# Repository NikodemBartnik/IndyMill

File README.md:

IndyMill is an open source DIY CNC machine that is mostly made out of metal. It was designed with simplicity and minimalism in mind! 
This project is not aiming to be the most heavy duty CNC machine out there, it is meant to be easy and inexpensive to build so that anyone can get a hand on precise CNC machining in many materials including metal.
Designed by [Nikodem Bartnik](https://www.youtube.com/nikodembartnik). 

Here are just some of the features of this machine:

  - Aluminium profiles (2080 and 2040)
  - Compatible with Nema17 and Nema23 on X and Y axis (without redesigning a plate Z axis is only compatible with Nema23)
  - Made with ball screws, linear rails and 6mm steel plates to ensure rigidity
  - Can be easily scaled up, you just need to use longer profiles, ballscrews and linear rails

***

### You can find more info at [Indystry.cc](https://indystry.cc/)

***

## Open Source
This machine is open source, so above you can find all of the files that you need to build it. You can also check out videos below to see the build process. As for now, the machine was tested with various kinds of wood, MDF, acrylic and aluminium. It is able to machine all of those materials even with a small 500W spindle.
You can also find more information on my website: [Indystry.cc](https://indystry.cc/indymill/)

## Parts

You can find parts list in PDF or XLSX above but you can also find it here:
  - At [indystry.cc/indymill](https://indystry.cc/indymill) you can find a full table with all needed parts
  - [Google Drive Parts List](https://docs.google.com/spreadsheets/d/19kC1wDViL0N2BjQgnNMfYSCzLNLKAHwQCY5Ngf8wU5I) here you can find an online parts list 
  - You can buy some of the parts on my [store](https://indystry.cc/store/)

## Videos

## Build Instruction
This project is open source so you can find all the files that you need to build it above for free. You can easily build it just by taking a look at some images on my website and my videos.
But if you would like to get a PDF instruction that simplifies the build process, you can easily print it put or it on a smartphone or computer. You can get one through link below and at the same time support my projects! You don't need it but it may help a little :)

### https://gum.co/indymill

### Todos

 - Design a better, bigger cable chain

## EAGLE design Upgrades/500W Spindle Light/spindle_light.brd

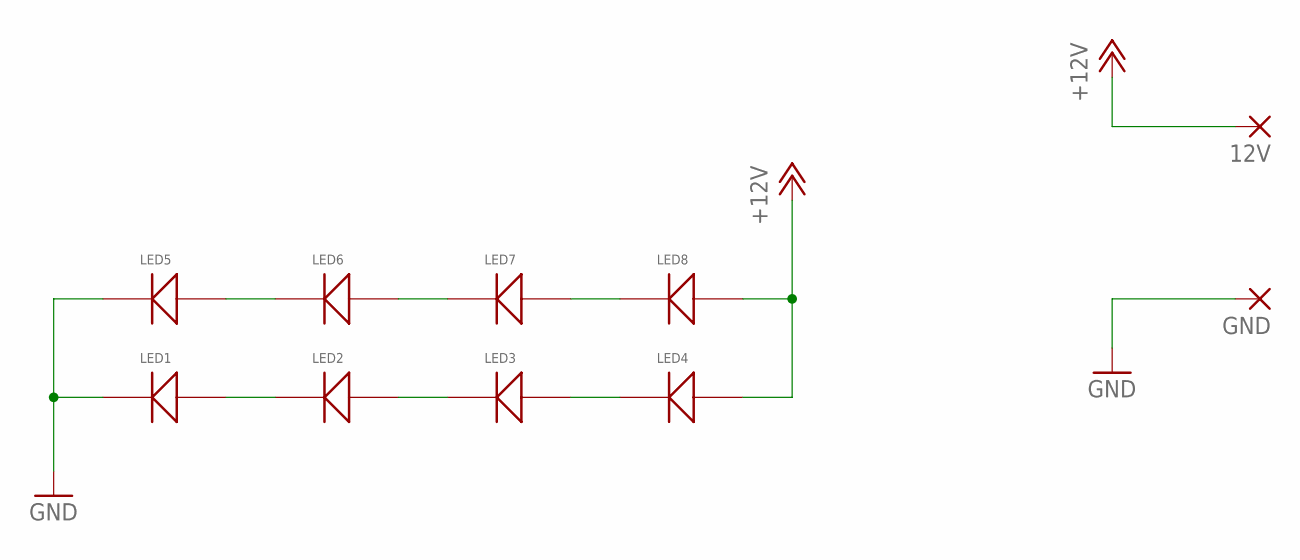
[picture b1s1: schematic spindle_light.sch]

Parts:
12V: SMD5; SMD2,54-5,08
GND: SMD5; SMD2,54-5,08
LED1, LED2, LED3, LED4, LED5, LED6, LED7, LED8: RF-45HA50DS-EE-Y; 5050LED

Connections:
+12V: 12V.1, LED4.P$4, LED4.P$5, LED4.P$6, LED8.P$4, LED8.P$5, LED8.P$6
GND: GND.1, LED1.P$1, LED1.P$2, LED1.P$3, LED5.P$1, LED5.P$2, LED5.P$3
unnamed: LED5.P$4, LED5.P$5, LED5.P$6, LED6.P$1, LED6.P$2, LED6.P$3
unnamed: LED1.P$4, LED1.P$5, LED1.P$6, LED2.P$1, LED2.P$2, LED2.P$3
unnamed: LED2.P$4, LED2.P$5, LED2.P$6, LED3.P$1, LED3.P$2, LED3.P$3
unnamed: LED6.P$4, LED6.P$5, LED6.P$6, LED7.P$1, LED7.P$2, LED7.P$3
unnamed: LED7.P$4, LED7.P$5, LED7.P$6, LED8.P$1, LED8.P$2, LED8.P$3
unnamed: LED3.P$4, LED3.P$5, LED3.P$6, LED4.P$1, LED4.P$2, LED4.P$3

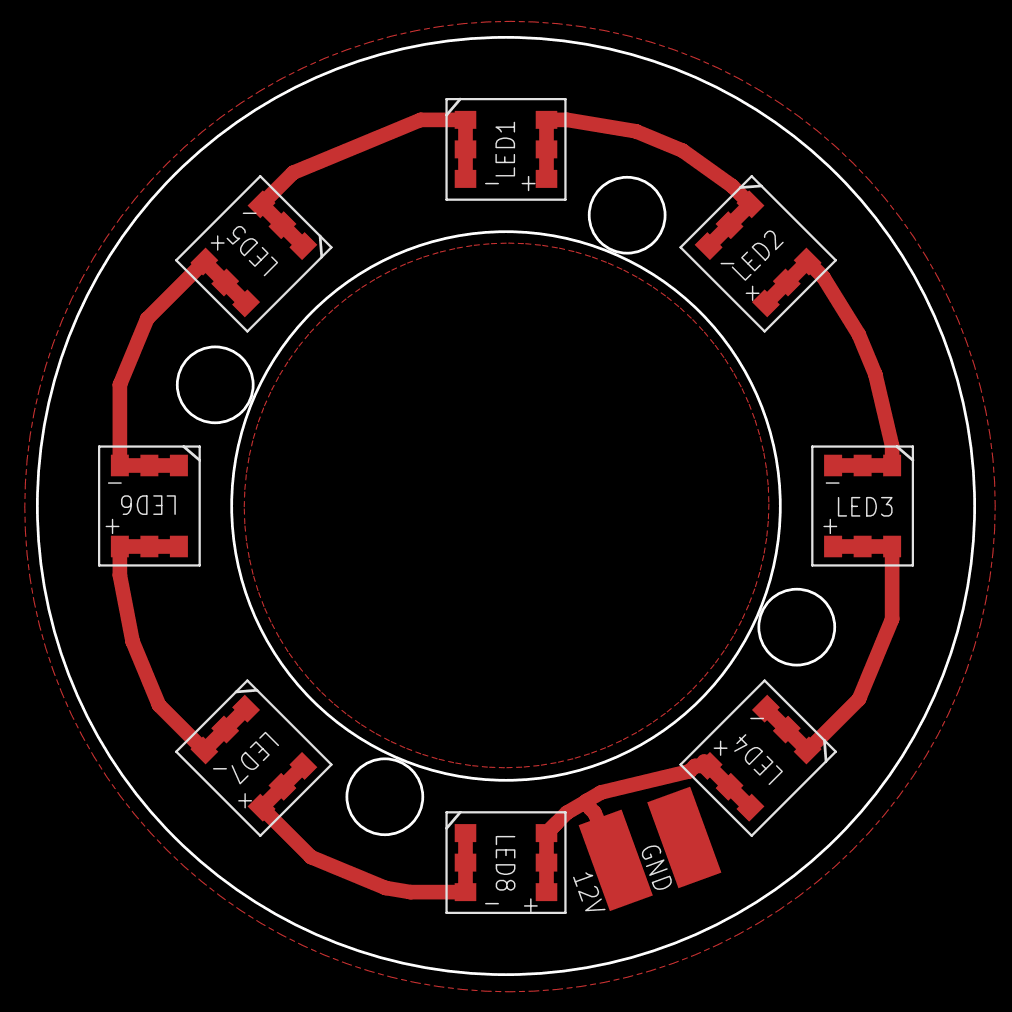
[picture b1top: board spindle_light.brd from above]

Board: 2 copper layers, 52.1 x 52.1 mm, 10 parts (0 on the bottom side), 8 nets.

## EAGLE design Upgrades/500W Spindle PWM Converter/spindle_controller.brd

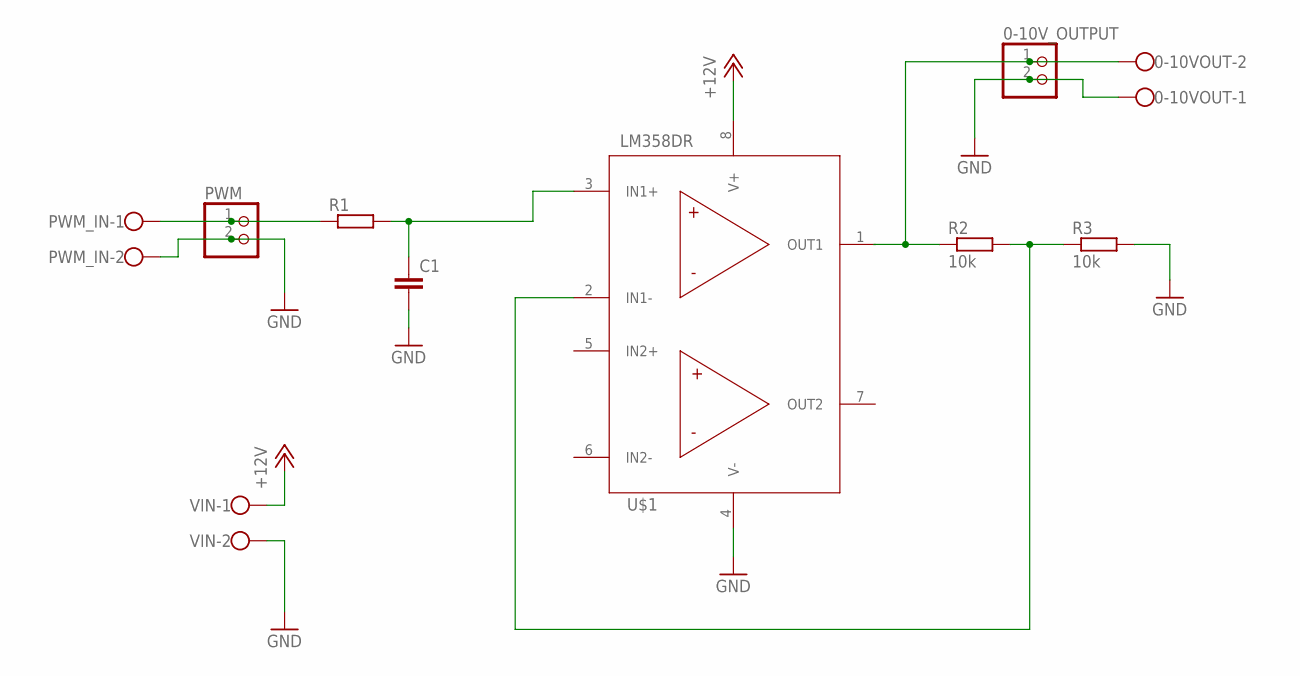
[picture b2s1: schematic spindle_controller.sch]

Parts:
0-10VOUT: W237-102
0-10V_OUTPUT: PINHD-1X2; 1X02
C1: C-EUC0603; C0603
PWM: PINHD-1X2; 1X02
PWM_IN: W237-102
R1: R-EU_R0603; R0603
R2, R3: 10k; R0603
U$1: LM358DRLM358DR_SOIC8; SOIC127P599X175-8N
VIN: W237-102

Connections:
+12V: U$1.8 (V+), VIN.1
GND: 0-10VOUT.1, 0-10V_OUTPUT.2, C1.2, PWM.2, PWM_IN.2, R3.2, U$1.4 (V-), VIN.2
unnamed: PWM.1, PWM_IN.1, R1.1
unnamed: C1.1, R1.2, U$1.3 (IN1+)
unnamed: R2.2, R3.1, U$1.2 (IN1-)
unnamed: 0-10VOUT.2, 0-10V_OUTPUT.1, R2.1, U$1.1 (OUT1)

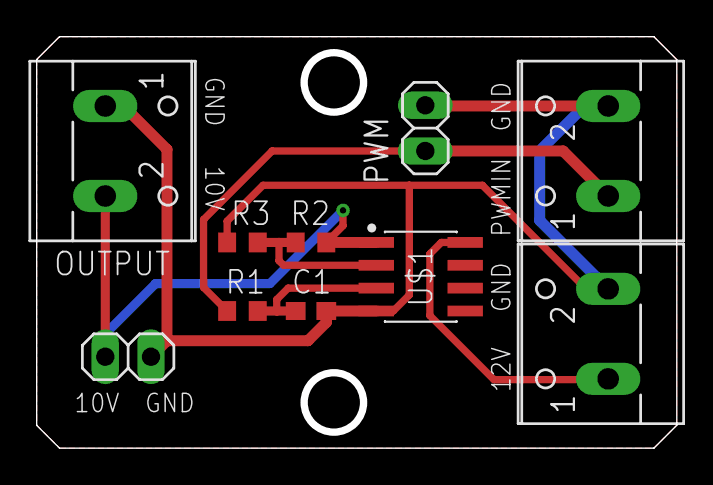
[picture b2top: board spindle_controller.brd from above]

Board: 2 copper layers, 35.6 x 22.9 mm, 10 parts (0 on the bottom side), 6 nets.

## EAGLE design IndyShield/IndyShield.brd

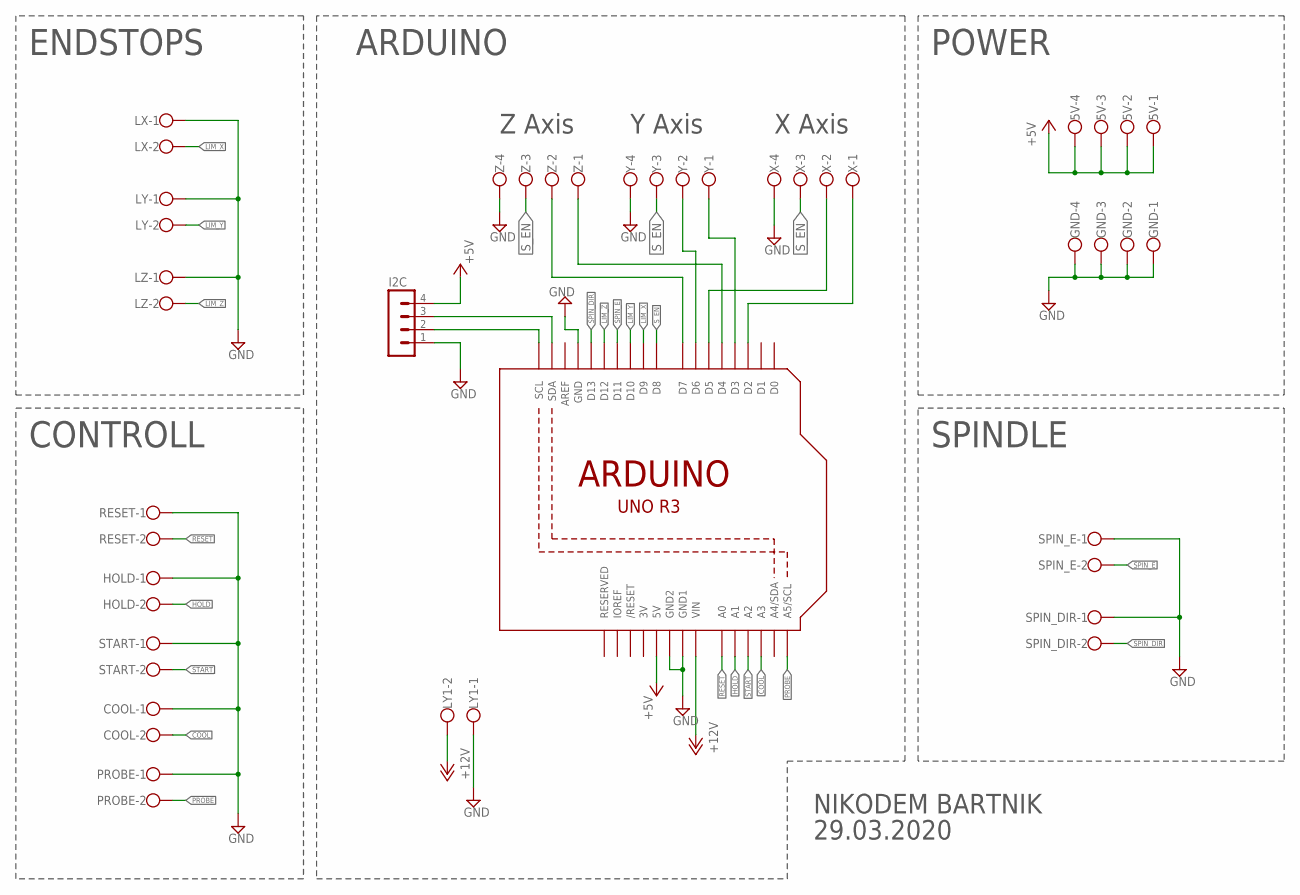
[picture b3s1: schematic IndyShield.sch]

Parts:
5V: W237-4
COOL: W237-102
GND: W237-4
HOLD: W237-102
I2C: MA04-1
LX: W237-102
LY, LY1: W237-102
LZ: W237-102
PROBE: W237-102
RESET: W237-102
SPIN_DIR: W237-102
SPIN_E: W237-102
START: W237-102
U1: ARDUINOR3-BPLACE
X: W237-4
Y: W237-4
Z: W237-4

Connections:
3V: U1.3V
+5V: 5V.1, 5V.2, 5V.3, 5V.4, I2C.4, U1.5V
+12V: LY1.2, U1.VIN
COOL: COOL.2, U1.A3
GND: COOL.1, GND.1, GND.2, GND.3, GND.4, HOLD.1, I2C.1, LX.1, LY.1, LY1.1, LZ.1, PROBE.1, RESET.1, SPIN_DIR.1, SPIN_E.1, START.1, U1.GND, U1.GND1, U1.GND2, X.4, Y.4, Z.4
HOLD: HOLD.2, U1.A1
LIM_X: LX.2, U1.D9
LIM_Y: LY.2, U1.D10
LIM_Z: LZ.2, U1.D12
unnamed: U1.D5, X.2
unnamed: U1.D2, X.1
unnamed: U1.D6, Y.2
unnamed: U1.D3, Y.1
unnamed: U1.D7, Z.2
unnamed: U1.D4, Z.1
unnamed: I2C.3, U1.SDA
unnamed: I2C.2, U1.SCL
PROBE: PROBE.2, U1.A5 (A5/SCL)
RESET: RESET.2, U1.A0
SPIN_DIR: SPIN_DIR.2, U1.D13
SPIN_E: SPIN_E.2, U1.D11
START: START.2, U1.A2
S_EN: U1.D8, X.3, Y.3, Z.3

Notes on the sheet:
X Axis
Y Axis
Z Axis
ENDSTOPS
SPINDLE
ARDUINO
POWER
CONTROLL
NIKODEM BARTNIK
29.03.2020

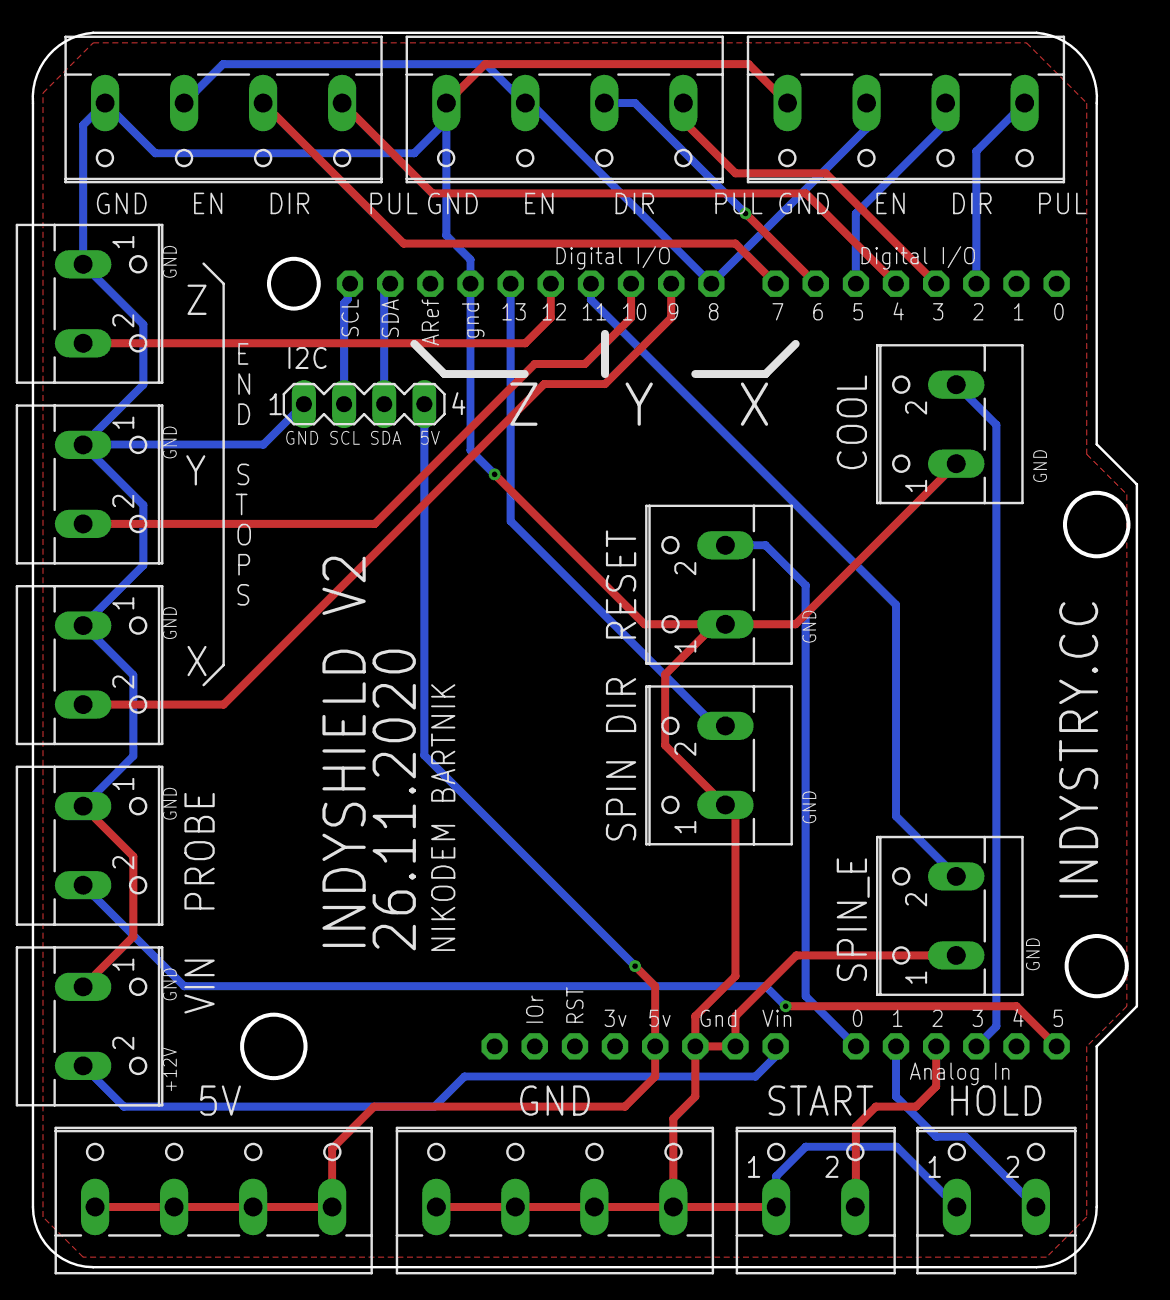
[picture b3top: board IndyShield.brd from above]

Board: 2 copper layers, 69.9 x 78.1 mm, 18 parts (0 on the bottom side), 22 nets.

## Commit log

2020-08-20 First commit
    First commit of all design files, PCB schematic and layout, electronics box and some other useful things
2020-09-06 [IndyMill] Updated project structure
2020-10-08 Ball screw covers STL
    Add balscrew covers STL files, small changes to some STL files
2021-02-12 Added dust shoe files
2021-02-17 Updated IndyShield to V2
    Swapped Z axis limit with spindle enable as it should be for current version of GRBL
2021-03-20 Smaller number of LEDs to make it a bit less bright
    Everything connected and prototyped working fine so far. Need to check the dimensions
2021-04-13 Laser cut part diagrams
2021-04-14 readme initial
2021-04-14 resize images
2021-05-01 Update to readme
2021-08-08 Redesign of 3D printed parts
2021-08-08 Added STEP files of all printed parts
2021-08-28 Updated BOM
2021-08-28 Updated TODO
2021-08-29 Added 500W spindle light and PWM converter. Also some clean up
2021-08-30 Spindle light update
2021-10-24 Redesign spindle light
2021-10-24 Squashed commit of the following:
    commit a86822d2883ca98a5418853accf885b86f3b1a4e
    Author: NikodemBartnik <nikodem.bartnik@gmail.com>
    Date: Sun Oct 24 13:37:13 2021 +0200
    typo fix
    commit 9fb647f2a9ac5ded72f7a5d88a2245ac32e2f947
    Author: NikodemBartnik <nikodem.bartnik@gmail.com>
2021-11-05 Clean up and new production files
2021-11-27 GND error fix
2022-02-08 Bigger X axis nut holder
2022-06-24 fixes small typos in README.md
2022-06-30 fixed some typos
2023-06-25 fix 3D printer friendly X axis block
2024-02-04 update dust shoe
2024-07-29 use correct image
